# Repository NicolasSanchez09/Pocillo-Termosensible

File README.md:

# Pocillo-Termosensible

## ¿Cuál es el problema a resolver?

Muchas veces al usar recipientes como pocillos u ollas desconocemos sus temperaturas. Esto puede ser peligroso si el contenido está muy caliente, ya que al consumirlo o manipularlo se podrían generar quemaduras. Si bien es cierto que a la gran mayoría nos ha ocurrido al menos una vez y no es nada de gravedad, además de ser incómodo, una exposición prologada a este tipo de heridas puede llegar a tener efectos negativos en la salud del individuo. De igual forma, si el contenedor es de un tamaño más grande, o  guarda algún material con una temperatura excesiva, se aumentaría la posibilidad de un accidente verdaderamente trágico. 

Es así que surge la idea de un pocillo termosensible, capaz de indicar con exactitud los grados a los cuales está el contenido del mismo, con el fin de exponerle la información al usuario y este se mantenga precavido. En un primer plano, la idea es aplicada a un pocillo de cerámica porque es uno de los elementos que se usan con más frecuencia a la hora de ingerir bebidas, sin embargo, en un futuro se podría desarrollar el proyecto en diferentes contextos como ollas, calderos, o incluso máquinas de producción industrial.

## ¿Cómo lo llevamos a cabo?

Tuvimos varios inconvenientes a la hora de materializar esta increíble idea, pero el primero fue pensar en los 'cómos';
 ¿Cómo vamos a medir la temperatura?, ¿cómo vamos a juntar todo?, ¿cómo vamos a notificar al usuario cuando su bebida esté lista?, ¿cómo vamos a diseñar la PCB?..

Con todas estas dudas en la cabeza, fuimos avanzando en el proyecto hasta resolverlas una por una. 
En primer lugar, decidimos medir la temperatura con una sonda de 3V, debidamente impermeable, para introducirla directamente en el pocillo cómo un pitillo. De otra forma, adaptamos la idea de modificar un pocillo, para diseñar un portavasos con todas las funcionalidadess integradas, que tuviera el hardware escondido en la zona inferior. Así pues, se lograría un producto más versátil, ya que podría adaptarse a diferentes tamaños y formas de pocillos, pero además más útil, porque al público se le haría más cómodo comprar un servicio extra que le sirve a lo que ya tiene, a tener que adquirir algo que nuevo con una funcionalidad de más. Por otra parte, para notificar al usuario, elegimos hacer uso de un pequeño display y un buzzer, periféricos de uso sencillo pero efectivo, que no solo mostrarán en pantalla de forma dinámica si la bebida está lista para consumo, sino que además alertarán al usuario cuando esta llegue a determinada temperatura. Finalmente, lo más difícil del proyecto fue definir cómo se iba a diseñar la PCB, para eso tuvimos que documentarnos profundamente acerca de la manufactura de esta tecnología, y realizar un boceto general del cómo se iba a conectar cada periférico a la ESP-32 de forma efectiva, y pequeña, puesto que las dimensiones de un pocillo estándar no son algo exageradas.

# Las distintas fases del Proyecto

Como bien se resaltó en el anterior apartado, el proceso de creación del proyecto tuvo distintos percances, así que daremos un recorrido guiado por las distintas y más importantes fases de este proceso: 

## Fase de *planeación*

En la que se dio solución a algunos de los "cómos" previamente enunciados. Por ejemplo, en esta fase de planeación, definimos las tecnologías que se ibana usar, haciendo uso del diagrama de caja negra:

Como se aprecia en la imagen, hasta ese momento, no se tenía contemplado el uso de un buzzer para notificar al usuario, pero fue una buena idea que surgió más adelante junto con otras más, la importancia de esta etapa recae, principalmente en que, al tener que mirar cómo se va a llevar a cabo el proyecto, nos dimos cuenta de las diferentes dificultades que conllevaba, y fuimos capaces de coregir los fallos para evolucionar hacia un resultado más eficiente.

Luego de realizar este diagrama, se decidió llevar a cabo el diagrama tecnológico, en el que se definiría concretamente qué dispositivo de hardware, ya sea sensor o actuador, se iba a usar para cada función como se puede ver en la siguiente imagen:

Ahora bien, en este punto aún no se ha añadido el buzzer al plan de acción, pero para mostrar cuál es el que se va a usar, adjuntaré link de compra en mercado libre y una foto: https://articulo.mercadolibre.com.co/MCO-608847377-buzzer-alarma-chicharra-3v-a-24v-dc-zumbador-grande-arduino-_JM#position=1&search_layout=stack&type=item&tracking_id=e0f2a067-7c86-415b-b5b0-ef70a2830b28

Una vez definidas las tecnologías con las que íbamos a trabajar, nos efrentábamos, sin saberlo, a la fase más difícil de este largo camino: La Fase de Acción.

## Fase de *acción*

Lo dicho, la fase más complicada del proceso. Al tratar de llevar todo a cabo y aterrizarlo al plano de la realidad, nos dimos cuenta de que realmente había mucho por corregir. Tuvimos que abandonar la idea de un pocillo como tal, debido a que no era práctico adicionar todo el hardware a un simple pocillo de cerámica, por sugerencia del profe, se decidió continuar con la misma idea pero desde una base para el pocillo, es decir, un portavasos con todas las funciones ya mencionadas. Se modeló la base y el soporte del display en OnShape para poderlo imprimir en PLA, se lo enviamos a El grandioso Carlos Mario, quien nos hizo el favor (a cambio de un módico precio) de imprimirlo. 

Ya estaba la base del proyecto hablando en términos generales, pero en términos electrónicos, no había una base, una PCB a la que se pudiera conectar todo para su correcto funcionamiento. Y es con esta, aparentemente, simple tarea, que el proyecto se complicó en gran medida.

Primero, realizar un diagrama de cómo se conectaría todo a la ESP-32, luego, estudiar cómo se transforma eso en una PCB, para finalmente, darnos cuenta de que estaba mal y tener que repetir ese mismo proceso al menos tres veces.

Finalmente, el diseño de las conecciones en Qucs quedó de la siguiente manera: 

Y, con este "boceto" de circuito, la PCB quedaría de la siguiente manera, representada en 3D gracias a las herramientas de simulación de KiCad

## Fase de manufactura y ensamble del proyecto

Fue la fase final del proyecto, en la que ya una vez pensado todo y con los materiales necesarios en nuestras manos, fuimos capaces de ensamblar todo en la protoboard, sí, la protoboard, porque la PCB tuvo un fallo que nadie supo explicar, al conectar la ESP-32 saltaba un error y no corría el código que previamente había funcionado. A pesar de esto, decidimos volver a intentar desarrollar una PCB funcional sin lo que, a nuestra forma de verlo y con nuestros limitados conocimientos, era el culpable de que la pcb no funcionara correctamente, pues es lo único diferente entre la PCB y la protoboard: la tarjeta controladora de la batería cd42-mh. Así que se diseñó una nueva pcb sin ese componente para poder llevar a cabo el proyecto satisfactoriamente.

Como se puede observar en la siguiente imagen, el prototipo funciona a la perfección sobre la protoboard:

Imagen de referencia de la nueva PCB corregida:

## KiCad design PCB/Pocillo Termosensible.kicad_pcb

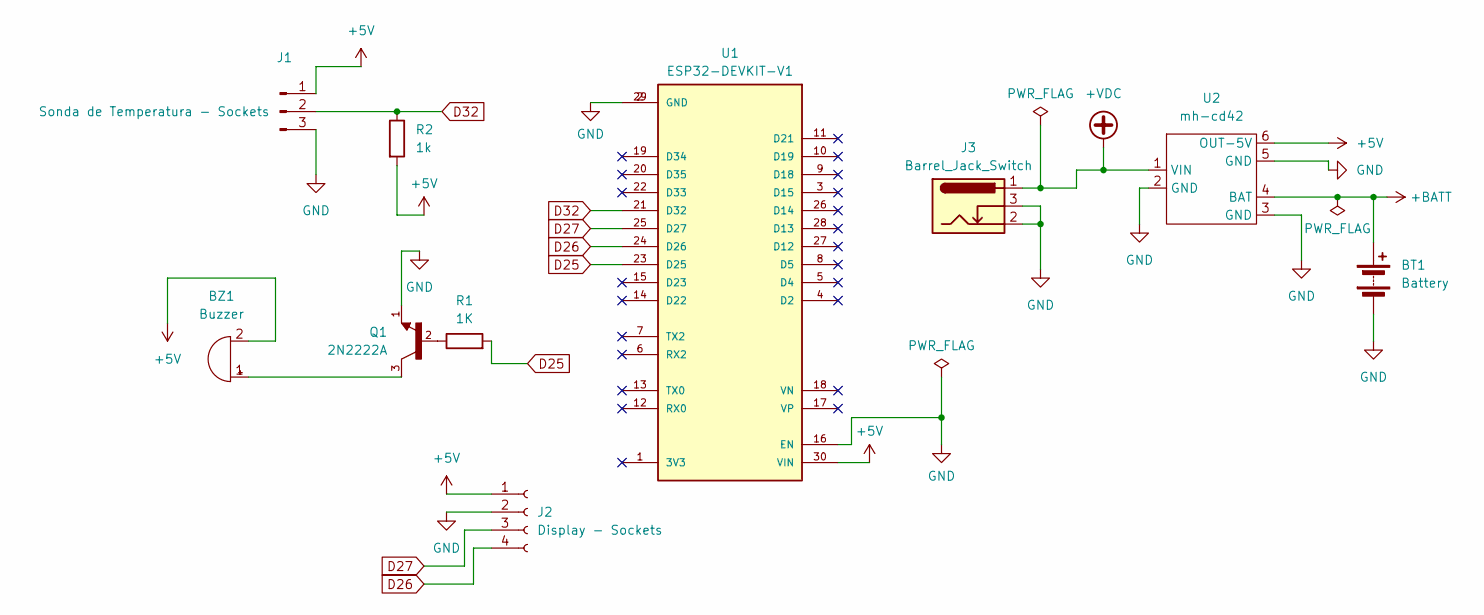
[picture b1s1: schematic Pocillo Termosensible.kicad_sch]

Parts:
BT1: Battery; BatteryHolder_MPD_BH-18650-PC2
BZ1: Buzzer; MagneticBuzzer_ProSignal_ABI-009-RC
J1: Sonda de Temperatura - Sockets; PinSocket_1x03_P2.54mm_Vertical
J2: Display - Sockets; PinSocket_1x04_P2.54mm_Vertical
J3: Barrel_Jack_Switch; BarrelJack_Horizontal
Q1: 2N2222A; TO92254P470H750-3; PARTREV N/A
R1: 1K; R_Axial_DIN0207_L6.3mm_D2.5mm_P10.16mm_Horizontal
R2: 1k; R_Axial_DIN0207_L6.3mm_D2.5mm_P10.16mm_Horizontal
U1: ESP32-DEVKIT-V1; MODULE_ESP32_DEVKIT_V1; PARTREV N/A
U2: mh-cd42

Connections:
+5V: BZ1.2 (+), J1.1, J2.1, R2.2, U1.30 (VIN), U2.6 (OUT-5V)
+BATT: BT1.1 (+), U2.4 (BAT)
+VDC: J3.1, U2.1 (VIN)
D25: R1.2, U1.23 (D25)
D26: J2.4, U1.24 (D26)
D27: J2.3, U1.25 (D27)
D32: J1.2, R2.1, U1.21 (D32)
GND: BT1.2 (-), J1.3, J2.2, J3.2, J3.3, Q1.1, U1.2 (GND), U1.16 (EN), U1.29 (GND), U2.2 (GND), U2.3 (GND), U2.5 (GND)
unnamed: BZ1.1 (-), Q1.3
unnamed: Q1.2, R1.1

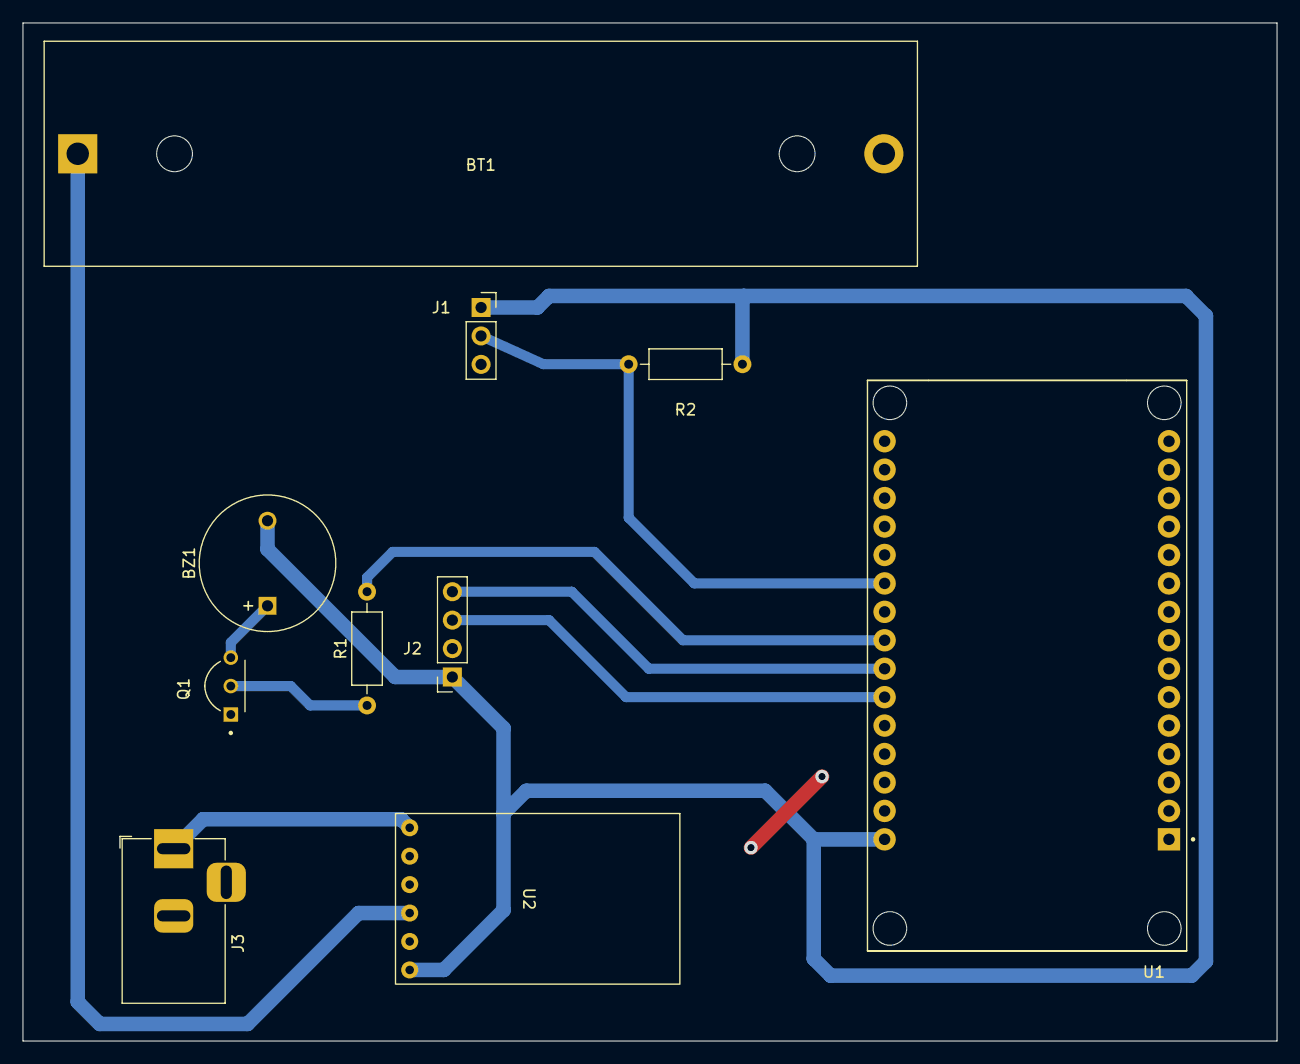
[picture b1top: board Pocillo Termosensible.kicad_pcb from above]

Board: 2 copper layers, 112.0 x 90.9 mm, 10 parts (0 on the bottom side), 10 nets.

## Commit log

2023-09-23 Desarrollo - Proyecto
2023-09-23 README.md
2023-11-08 <Update>README.md
2023-12-01 Create Case
2023-12-01 Update Case
